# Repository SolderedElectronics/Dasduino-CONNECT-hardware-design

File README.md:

# Dasduino CONNECT Hardware Design

## About the Product

|  |
| :----------------------------------------------------------: |
| [Buy Dasduino CONNECT](https://www.solde.red/333034) |

The biggest advantage of Dasduino Connect hides within its name. If you ever wanted to connect your development board directly to the Internet, look no further! This Dasduino comes with the ability to connect to Wi-Fi. It even comes with the TCP/IP protocol suite that supports DNS. Connecting the physical world with the Internet has never been easier! Dasduino Connect is based on the well-known ESP8266 microchip which can be a bit complicated to use on its own. Adding the fact that it works from the Arduino IDE, working this board is as simple as it gets.

Dasduino Connect is 71 mm wide and 26 mm high so you can fit it in most projects. It fits perfectly on a breadboard for faster prototyping. It has a total of 30 pins, most of which are digital and one of which is analog. You can simply connect it to your computer with a USB Type-C and program it in Arduino IDE. Connecting the Dasduino Connect with other boards is done with an qwiic cable. The design is 3.3V ready with an onboard regulator for 5V. With the JST battery connector, you can make your projects truly wireless. It includes full RGB WS2812B LED as well. Comes without any headers although it comes with USB-C cable.
---

## Repository Contents

This repository contains all design files for Dasduino CONNECT, organized as follows:

- **`CAD` folder**: Contains KiCAD design files, including:
  - Schematics
  - PCB layout
  - Panel PCB layout
  - Source 3D files in Fusion360, if any
  - All files are sorted by version with a detailed change log.
- **`OUTPUTS` folder**: Includes all production-ready files, such as:
  - Bill of Materials (BOM) and interactive BOM (iBOM)
  - PDF versions of schematics
  - 3D `.step` file of the board
  - 3D-printable models
  - Gerber files for PCB manufacturing
  - Image of the pinout of the board
  - Product image
  - Compliance, legal and generic sales documents

Refer to the `Change Log` in the CAD folder for details about updates between versions.

---

## Learn More About the Product

Beyond the repository, explore the following resources:

### Soldered Verify

The **Soldered Verify** system ensures every board you purchase from Soldered is fully functional. It also provides access to exclusive test data for your product. To get started, find the unique Soldered Verify ID on your product's packaging and enter the ID on the [Soldered Verify page](https://soldered.com/verify/) to access test results and additional product details.

### Soldered Community

Soldered Community is your go-to place for technical support. Our engineers track and answer all questions posted there, and it’s a great space for the maker community. Get answers to your questions and solutions for your challenges at [Soldered Community](https://soldered.com/community).

### solde.red

solde.red is an ultimate URL shortener and information hub. Access it by typing solde.red/ followed by your product SKU, e.g., [solde.red/333000](https://solde.red/333000), to find getting-started guides, datasheets, open-source hardware and software files, certifications, images, pinouts, and more. Read more about the shortener [here](https://solde.red/info/).

---

## Contributing

Contributions are welcome! Here’s how you can get involved:

- Submit pull requests to enhance the design or fix issues.
- Report bugs or problems by opening an issue.

We encourage community collaboration to make this product even better.

---

## About Soldered

[Soldered for Makers](https://soldered.com) specializes in designing and manufacturing electronic products tailored for enthusiasts, ranging from hobbyists to professionals. Our portfolio includes electronic boards, sensors, and actuators that are widely utilized in fields such as microelectronics, mechatronics, robotics, programming, and IoT. Every product we offer is designed in-house and built upon open-source hardware and software platforms. Proudly certified and manufactured within the European Union, our catalog likely includes the product you need for your project.

We complement these products with comprehensive tutorials and manuals, product descriptions, schematics, programming codes, and project examples. Our round-the-clock [customer and technical support](https://soldered.com/community) is available for all our products, irrespective of the sales channel. Soldered’s success and services reflect our maker community’s unwavering [trust](https://www.trustpilot.com/review/soldered.com), for which we are deeply grateful. Join our community and create using Soldered products.

---

## License

All Soldered open-source hardware (OSH) is under The TAPR Open Hardware License. Read more in the LICENSE file located in this repository.

**Disclaimer:**

No warranty - all designs in this repository are distributed in the hope that they will be useful, but without any warranty. They are provided "AS IS", therefore without warranty of any kind, either expressed or implied. The entire quality and performance of what you do with the contents of this repository are your responsibility. In no event Soldered Electronics will be liable for your damages, or losses, including any general, special, incidental, or consequential damage arising out of the use or inability to use the contents of this repository. 

---

## Have fun!

Thank you for your support from your fellow makers at Soldered Electronics.

Happy Making!

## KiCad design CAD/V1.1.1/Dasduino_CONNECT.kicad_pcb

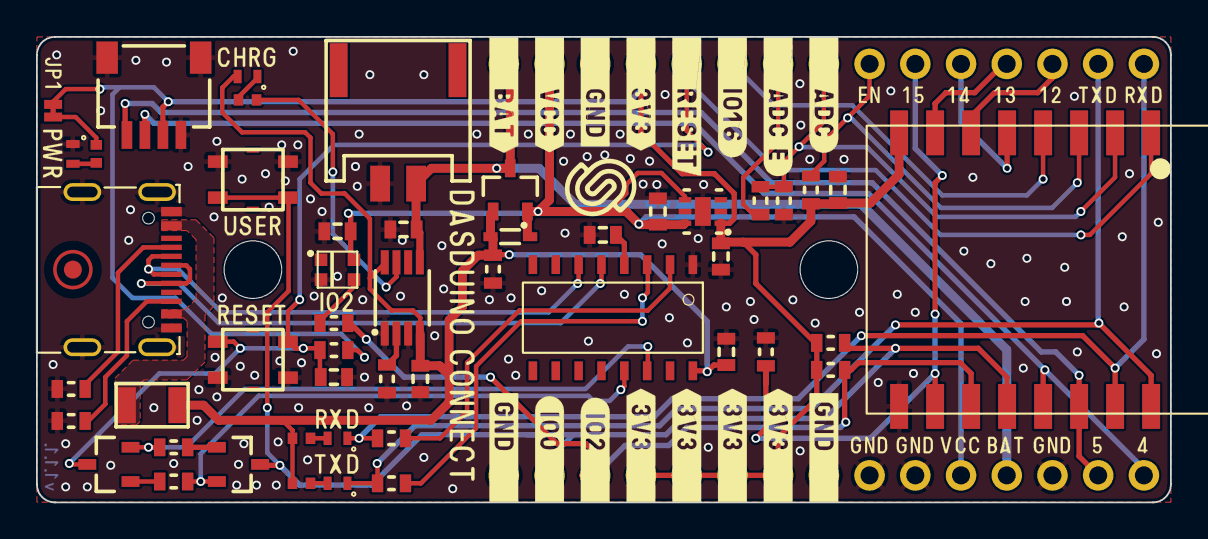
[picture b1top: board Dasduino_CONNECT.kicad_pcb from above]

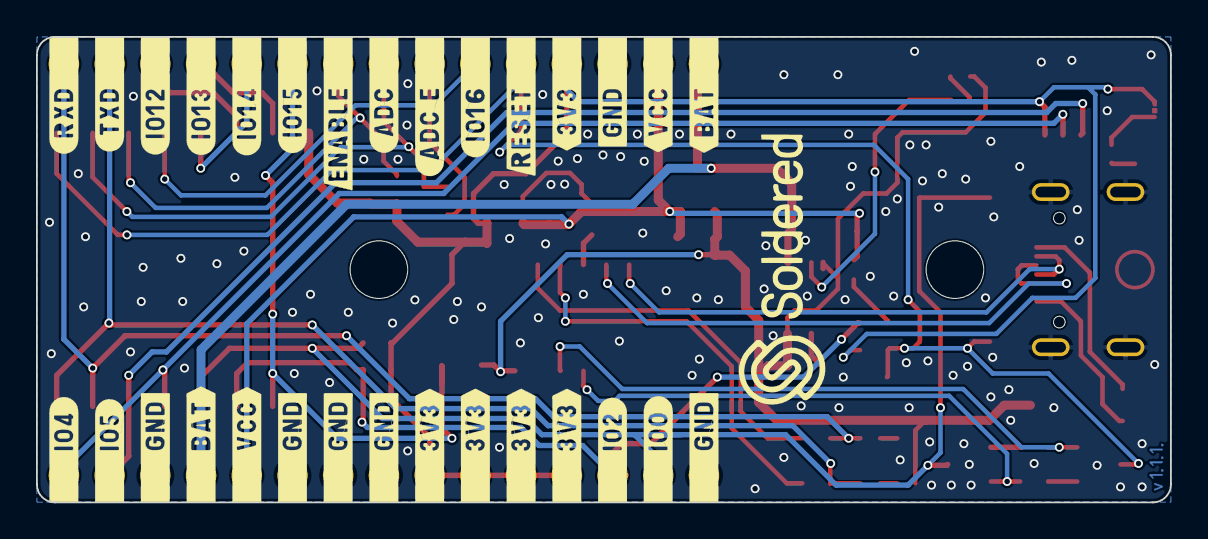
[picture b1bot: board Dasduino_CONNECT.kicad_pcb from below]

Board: 2 copper layers, 63.0 x 25.9 mm, 54 parts (2 on the bottom side), 40 nets.

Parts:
C1, C2: 0.1uF; 0603C
C3, C5, C7, C8: 2.2uF; 0603C
C4, C9: 100nF; 0603C
C6: 270pF; 0603C
D1: white; 0402LED
D2: blue; 0402LED
D3: purple; 0402LED
D4: WS2812B-2020
D5: red; 0402LED
D7: BAT20J; SOD-323
F1: 1206FUSE-500mA; 1206FUSE
FD1: FIDUCIAL; FIDUCIAL_23
H1, H2: HOLE_3.2mm
JP1: SMD-JUMPER-CONNECTED_TRACE_SLODERMASK
K1: easyC-SMD; easyC-connector
K2: U262-161N-4BVC11
K3: JST-2pin-SMD
K4, K5: HEADER_MALE_15X1
Q1: PMOS-SOT-23-3; SOT-23-3
Q2, Q3: NPN-SOT-23-3; SOT-23-3
R1, R2, R5: 1k; 0603R
R3, R4, R6, R12: 2k2; 0402R
R7, R8: 5.1k; 0603R
R9, R10, R16, R17, R18, R19, R20, R21: 10k; 0603R
R11: 3k; 0603R
R14: 100k; 0603R
R15: 2k49; 0603R
SW1, SW2: YTSA007A0151803B
U1: CH340C; SOP-16
U2: TPS7A2633DRVR
U3: TP4056M; TP4056M-MSOP8
U4: ESP8266(ESP12-F); ESP 8266(ESP12-F)

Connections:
+3V3: C5.2, C9.2, JP1.1, K1.3 (3V3), K4.4, K5.4, K5.5, K5.6, K5.7, R10.2, R16.2, R17.2, R18.2, U2.1 (OUT), U4.8 (VCC)
ADC: K4.8, R9.1, R15.2, U4.2 (ADC)
ADC_E: K4.7, R9.2
CH_PD: K4.9, R17.1, U4.3 (EN)
D+: K2.A6 (DP1), K2.B6 (DP2), U1.5 (UD+)
D-: K2.A7 (DN1), K2.B7 (DN2), U1.6 (UD-)
DTR: Q3.2 (E), R20.1, U1.13 (DTR#)
GND: C1.1, C2.2, C3.1, C4.2, C5.1, C6.1, C7.1, C8.1, C9.1, D3.2 (K), D4.2 (GND), K1.4 (GND), K1.5 (SHIELD), K2.A1 (GND), K2.A12 (GND), K2.B1 (GND), K2.B12 (GND), K2.SH (SHIELD), K3.2 (-), K4.3, K5.1, K5.8, K5.9, K5.10, K5.13, R7.2, R8.2, R11.2, R14.1, R15.1, R19.1, SW1.1, SW2.2, U1.1 (GND), U2.5 (GND), U3.1 (TEMP), U3.3 (GND), U4.9 (GND)
IO0: K5.2, Q3.3 (C), R18.1, SW1.2, U4.12 (GPIO0)
IO2: K5.3, R5.1, R16.1, U4.11 (GPIO2)
IO16: K4.6, U4.4 (GPIO16)
unnamed: C2.1, U1.4 (V3)
unnamed: D1.1 (A), R3.1
unnamed: D2.1 (A), R4.1
unnamed: D3.1 (A), R6.2
unnamed: D4.3 (DI), R5.2
unnamed: D5.2 (K), R12.2
unnamed: F1.2, K2.A4 (VBUS), K2.A9 (VBUS), K2.B4 (VBUS), K2.B9 (VBUS)
unnamed: JP1.2, R6.1
unnamed: K2.A5 (CC1), R8.1
unnamed: K2.B5 (CC2), R7.1
unnamed: Q2.1 (B), R20.2
unnamed: Q3.1 (B), R21.2
unnamed: R1.1, U1.2 (TXD)
unnamed: R2.1, U1.3 (RXD)
unnamed: R11.1, U3.2 (PROG)
unnamed: R12.1, U3.7 (~CHRG)
RESET: C6.2, K4.5, Q2.3 (C), R10.1, SW2.1, U4.1 (RST)
RTS: Q2.2 (E), R21.1, U1.14 (RTS#)
RXD0: D2.2 (K), K4.15, R1.2, U4.15 (RXD)
SCL: K1.1 (SCL), K5.14, U4.14 (GPIO5)
SDA: K1.2 (SDA), K5.15, U4.13 (GPIO4)
SPI_CS: K4.10, R19.2, U4.10 (GPIO15)
SPI_MISO: K4.13, U4.6 (GPIO12)
SPI_MOSI: K4.12, U4.7 (GPIO13)
SPI_SCK: K4.11, U4.5 (GPIO14)
TXD0: D1.2 (K), K4.14, R2.2, U4.16 (TXD)
VBAT: C7.2, K3.1 (+), K4.1, K5.12, Q1.3 (D), U3.5 (BAT)
VCC: C3.2, C4.1, D4.4 (VDD), D7.2 (K), K4.2, K5.11, Q1.2 (S), U2.4 (EN), U2.6 (IN)
VUSB: C1.2, C8.2, D5.1 (A), D7.1 (A), F1.1, Q1.1 (G), R3.2, R4.2, R14.2, U1.16 (VCC), U3.4 (VCC), U3.8 (CE)

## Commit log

2022-08-06 Updating open source files.
